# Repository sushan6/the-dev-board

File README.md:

# Sushan's dev board 

This development board is designed to be a compact, reliable prototyping platform using the RP2040 microcontroller. It handles power management, high-speed external memory routing, and precise clocking, making it ready for custom embedded software applications.

## Key Features

* Microcontroller: Based on the RP2040 chip, bringing twin-core processing capabilities to a custom hardware layout.
* Power Management: Driven by a modern USB-C receptacle for both power delivery and data interfacing, regulated down to a clean three-point-three volts using an onboard linear regulator.
* External Storage: Incorporates external flash memory connected over a quad serial peripheral interface, giving ample room for large programs and data storage.
* Clock Source: Utilises a twelve megahertz crystal oscillator circuit to ensure stable and highly accurate clock timing for the microcontroller.
* Input and Output Breakouts: Exposes general-purpose input/output pins to dual-row pin headers, providing quick access for connecting sensors, displays, and external components.
* There are 40 pins externally for data
* SD card reader 
## Hardware Design and Previews

### Schematic Layout
The schematic is divided into clean functional blocks including power management, flash memory wiring, crystal clock generation, and pin mappings. 

---

### PCB Layout and 3D Visualisations
The physical layout focuses on tight trace routing, proper decoupling capacitor placement for power stability, and optimised signal paths. 

#### Board Front View

#### Board Back View

## Bill of Materials (BOM)

### Main BOM

| **Item** | **Link** | **Quantity** | **Cost (USD)** |
|---|---|---:|---:|
| 1 µF Capacitors (0402) | [Robu.in](https://robu.in/product/1uf-capacitor-smdc-0402-pack-of-50/) | 20 | $0.06 |
| 100 nF Capacitors (0402) | [Robu.in](https://robu.in/product/0402b104j250nt-fh-25v-100nf-x7r%C2%B15-0402-multilayer-ceramic-capacitors-mlcc-smd-smt-rohs/) | 20 | $0.14 |
| 10 µF Capacitors (0603) | [Robu.in](https://robu.in/product/0603x106m100nt-fh-10v-10uf-x5r%C2%B120-0603-multilayer-ceramic-capacitors-mlcc-smd-smt-rohs/) | 20 | $0.53 |
| 33 pF Capacitors (0402) | [Robu.in](https://robu.in/product/0402cg330j160nt-fh-smd-multilayer-ceramic-capacitor-33-pf-16-v-0402-1005-metric-%25c2%25b1-5-c0g-np0/) | 20 | $0.01 |
| USB-C Receptacles | [LCSC India](https://lcscindia.com/part/TYPE-C-31-M-12) | 2 | $0.45 |
| 1×20 Pin Headers | [Robu.in](https://robu.in/product/ds1021-1x20sf11-b-connfly-1x20-pin-2-54mm-pin-header-v-t-type/) | 4 | $0.55 |
| MicroSD Card Connectors | [RS India](https://in.rsdelivers.com/product/molex/104031-0811/molex-104031-8-way-push-pull-microsd-memory-card/8967560) | 2 | $4.68 |
| 5.1 kΩ Resistors (0402) | [Robu.in](https://robu.in/product/rc0402fr-075k1l-yageo-res-thick-film-0402-5-1k-ohm-1-0-063w1-16w-%C2%B1100ppm-c-pad-smd-t-r/) | 20 | $0.05 |
| 27 Ω Resistors (0402) | [Robu.in](https://robu.in/product/rc0402jr-0727rl-yageo-res-thick-film-0402-27-ohm-5-0-063w1-16w-%25c2%25b1100ppm-c-pad-smd-t-r/) | 20 | $0.02 |
| 1 kΩ Resistors (0402) | [Robu.in](https://robu.in/product/rc0402fr-071kl-yageo-res-thick-film-0402-1k-ohm-1-0-063w1-16w-%C2%B1100ppm-c-pad-smd-t-r/) | 20 | $0.03 |
| 10 kΩ Resistors (0402) | [Robu.in](https://robu.in/product/10k-resistor-smdr-0402-pack-of-50/) | 20 | $0.07 |
| Tactile Switches | [Robu.in](https://robu.in/product/tsa010a2026b-bzcn-3mm-2mm-50ma-round-button-standing-paste-3-9mm-260gf-12v-smd-tactile-switches-rohs/) | 2 | $0.04 |
| RP2040 Microcontrollers | [Robocraze](https://robocraze.com/products/raspberry-pi-rp2040-microcontroller-ic-chip) | 2 | $1.36 |
| 3.3V Voltage Regulators | [Microchip](https://www.microchip.com/en-us/product/MCP1700) | 2 | $1.20 |
| 16 Mbit SPI Flash | [Lion Circuits](https://www.lioncircuits.com/parts/W25Q16JVUXIQ%20TR) | 2 | $4.88 |
| 12 MHz Crystals | [Robu.in](https://robu.in/product/ysx321sl-12mhz-12pf-10ppm-4pins-smd-smt-metal-surface-quartz-crystal-pack-of-2/) | 2 | $0.43 |
| Soldering Starter Kit | [Robu.in](https://robu.in/product/soldering-starter-tool-kit-30w-iron-solder-sponge/) | 1 | $13.30 |
| Custom PCB | [JLCPCB](https://jlcpcb.com/) | 2 | $15.00 |

### Cost Summary

| **Item** | **Cost (USD)** |
|---|---:|
| Capacitors (20 each) | $0.75 |
| Resistors (20 each) | $0.16 |
| USB-C Receptacles | $0.45 |
| 1×20 Pin Headers | $0.55 |
| MicroSD Connectors | $4.68 |
| Tactile Switches | $0.04 |
| RP2040 Microcontrollers | $1.36 |
| Voltage Regulators | $1.20 |
| SPI Flash Memory | $4.88 |
| 12 MHz Crystals | $0.43 |
| Soldering Starter Kit | $13.30 |
| PCB Fabrication | $15.00 |
| **Total** | **$42.80** |

Note: Some items are ordered in multipe quantity because of minimum order value

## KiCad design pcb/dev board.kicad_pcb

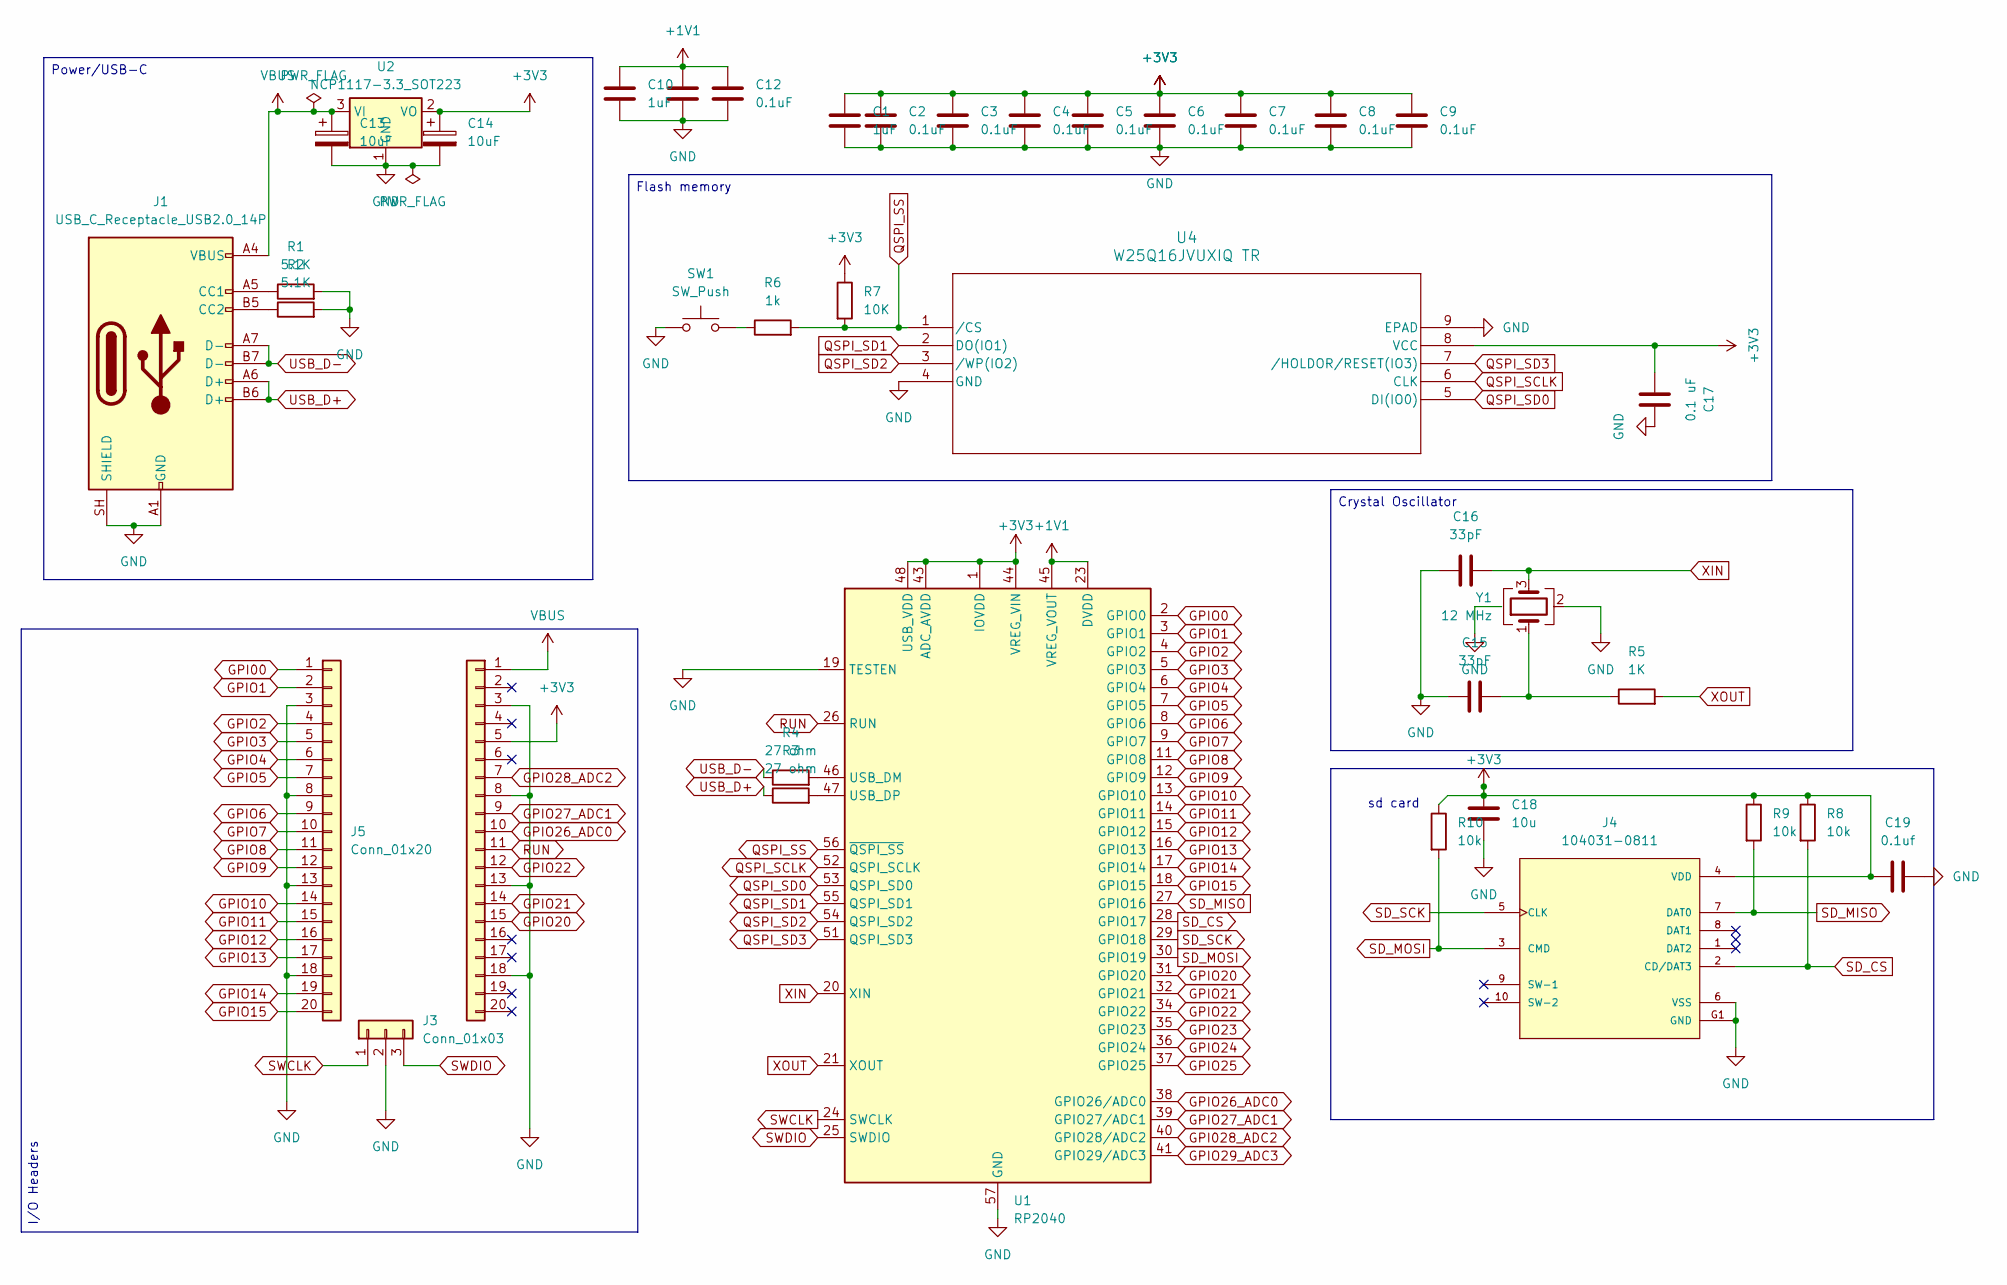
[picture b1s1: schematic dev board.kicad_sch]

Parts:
C1, C10: 1uF; C_0402_1005Metric
C2, C3, C4, C5, C6, C7, C8, C9, C11, C12: 0.1uF; C_0402_1005Metric
C13, C14: 10uF; C_0603_1608Metric
C15, C16: 33pF; C_0402_1005Metric
C17: 0.1 uF; C_0402_1005Metric
C18: 10u; C_0603_1608Metric
C19: 0.1uf; C_0402_1005Metric
J1: USB_C_Receptacle_USB2.0_14P; USB_C_Receptacle_HRO_TYPE-C-31-M-12
J2, J5: Conn_01x20; PinHeader_1x20_P2.54mm_Vertical
J3: Conn_01x03; PinHeader_1x03_P1.27mm_Vertical_SMD_Pin1Left
J4: 104031-0811; microSD_HC_Molex_104031-0811; PARTREV B2
R1, R2: 5.1K; R_0402_1005Metric
R3, R4: 27 ohm; R_0402_1005Metric
R5: 1K; R_0402_1005Metric
R6: 1k; R_0402_1005Metric
R7: 10K; R_0402_1005Metric
R8, R9, R10: 10k; R_0402_1005Metric
SW1: SW_Push; SW_Push_SPST_NO_Alps_SKRK
U1: RP2040; QFN-56-1EP_7x7mm_P0.4mm_EP3.2x3.2mm
U2: NCP1117-3.3_SOT223; SOT-23
U4: W25Q16JVUXIQ TR; Winbond_USON-8-1EP_3x2mm_P0.5mm_EP0.2x1.6mm
Y1: 12 MHz; Crystal_SMD_3225-4Pin_3.2x2.5mm

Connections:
+1V1: C10.1, C11.1, C12.1, U1.23 (DVDD), U1.45 (VREG_VOUT), U1.50 (DVDD)
+3V3: C1.1, C2.1, C3.1, C4.1, C5.1, C6.1, C7.1, C8.1, C9.1, C14.1, C17.1, C18.1, C19.2, J2.5, J4.4 (VDD), R7.1, R8.1, R9.1, R10.1, U1.1 (IOVDD), U1.10 (IOVDD), U1.22 (IOVDD), U1.33 (IOVDD), U1.42 (IOVDD), U1.43 (ADC_AVDD), U1.44 (VREG_VIN), U1.48 (USB_VDD), U1.49 (IOVDD), U2.2 (VO), U4.8 (VCC)
GND: C1.2, C2.2, C3.2, C4.2, C5.2, C6.2, C7.2, C8.2, C9.2, C10.2, C11.2, C12.2, C13.2, C14.2, C15.1, C16.1, C17.2, C18.2, C19.1, J1.A1 (GND), J1.A12 (GND), J1.B1 (GND), J1.B12 (GND), J1.SH (SHIELD), J2.3, J2.8, J2.13, J2.18, J3.2, J4.6 (VSS), J4.G1 (GND), J4.G2 (GND), J4.G3 (GND), J4.G4 (GND), J5.3, J5.8, J5.13, J5.18, R1.2, R2.2, SW1.1, U1.19 (TESTEN), U1.57 (GND), U2.1 (GND), U4.4 (GND), U4.9 (EPAD), Y1.2 (G), Y1.4 (G)
GPI00: J5.1
GPI028_ADC2: U1.40 (GPIO28/ADC2)
GPIO0: U1.2 (GPIO0)
GPIO1: J5.2, U1.3 (GPIO1)
GPIO2: J5.4, U1.4 (GPIO2)
GPIO3: J5.5, U1.5 (GPIO3)
GPIO4: J5.6, U1.6 (GPIO4)
GPIO5: J5.7, U1.7 (GPIO5)
GPIO6: J5.9, U1.8 (GPIO6)
GPIO7: J5.10, U1.9 (GPIO7)
GPIO8: J5.11, U1.11 (GPIO8)
GPIO9: J5.12, U1.12 (GPIO9)
GPIO10: J5.14, U1.13 (GPIO10)
GPIO11: J5.15, U1.14 (GPIO11)
GPIO12: J5.16, U1.15 (GPIO12)
GPIO13: J5.17, U1.16 (GPIO13)
GPIO14: J5.19, U1.17 (GPIO14)
GPIO15: J5.20, U1.18 (GPIO15)
GPIO20: J2.15, U1.31 (GPIO20)
GPIO21: J2.14, U1.32 (GPIO21)
GPIO22: J2.12, U1.34 (GPIO22)
GPIO23: U1.35 (GPIO23)
GPIO24: U1.36 (GPIO24)
GPIO25: U1.37 (GPIO25)
GPIO26_ADC0: J2.10, U1.38 (GPIO26/ADC0)
GPIO27_ADC1: J2.9, U1.39 (GPIO27/ADC1)
GPIO28_ADC2: J2.7
GPIO29_ADC3: U1.41 (GPIO29/ADC3)
unnamed: C15.2, R5.1, Y1.1
unnamed: J1.A5 (CC1), R1.1
unnamed: J1.B5 (CC2), R2.1
unnamed: R6.1, SW1.2
unnamed: R4.2, U1.46 (USB_DM)
unnamed: R3.2, U1.47 (USB_DP)
QSPI_SCLK: U1.52 (QSPI_SCLK), U4.6 (CLK)
QSPI_SD0: U1.53 (QSPI_SD0), U4.5 (DI(IO0))
QSPI_SD1: U1.55 (QSPI_SD1), U4.2 (DO(IO1))
QSPI_SD2: U1.54 (QSPI_SD2), U4.3 (/WP(IO2))
QSPI_SD3: U1.51 (QSPI_SD3), U4.7 (/HOLDOR/RESET(IO3))
QSPI_SS: R6.2, R7.2, U1.56 (~QSPI_SS), U4.1 (/CS)
RUN: J2.11, U1.26 (RUN)
SD_CS: J4.2 (CD/DAT3), R8.2, U1.28 (GPIO17)
SD_MISO: J4.7 (DAT0), R9.2, U1.27 (GPIO16)
SD_MOSI: J4.3 (CMD), R10.2, U1.30 (GPIO19)
SD_SCK: J4.5 (CLK), U1.29 (GPIO18)
SWCLK: J3.1, U1.24 (SWCLK)
SWDIO: J3.3, U1.25 (SWDIO)
USB_D+: J1.A6 (D+), J1.B6 (D+), R3.1
USB_D-: J1.A7 (D-), J1.B7 (D-), R4.1
VBUS: C13.1, J1.A4 (VBUS), J1.A9 (VBUS), J1.B4 (VBUS), J1.B9 (VBUS), J2.1, U2.3 (VI)
XIN: C16.2, U1.20 (XIN), Y1.3
XOUT: R5.2, U1.21 (XOUT)

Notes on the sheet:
sd card
Power/USB-C
I/O Headers
Flash memory
Crystal Oscillator

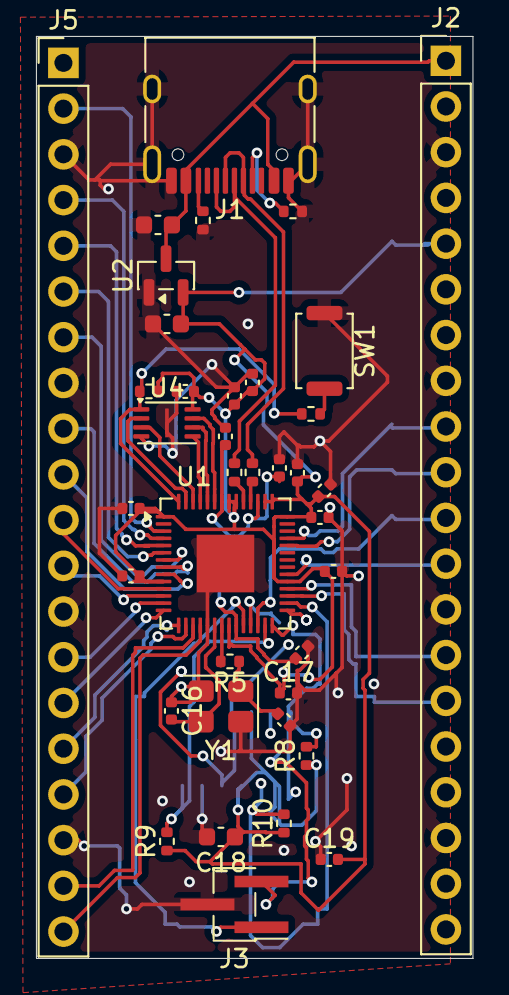
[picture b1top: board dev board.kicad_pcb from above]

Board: 4 copper layers, 24.2 x 51.2 mm, 39 parts (1 on the bottom side), 47 nets.

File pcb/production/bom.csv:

Designator,Footprint,Quantity,Value,LCSC Part #
"C1, C10",0402,2,1uF,
"C11, C12, C2, C3, C4, C5, C6, C7, C8, C9",0402,10,0.1uF,
"C13, C14",0603,2,10uF,
"C15, C16",0402,2,33pF,
C17,0402,1,0.1 uF,
J1,USB_C_Receptacle_HRO_TYPE-C-31-M-12,1,USB_C_Receptacle_USB2.0_14P,
"J2, J5",PinHeader_1x20_P2.54mm_Vertical,2,Conn_01x20,
J3,PinHeader_1x03_P2.54mm_Vertical,1,Conn_01x03,
"R1, R2",0402,2,5.1K,
"R3, R4",0402,2,27 ohm,
"R5, R6",0402,2,1K,
R7,0402,1,10K,
SW1,SW_Push_SPST_NO_Alps_SKRK,1,SW_Push,
U1,QFN-56-1EP_7x7mm_P0.4mm_EP3.2x3.2mm,1,RP2040,
U2,SOT-23,1,NCP1117-3.3_SOT223,
U4,Winbond_USON-8-1EP_3x2mm_P0.5mm_EP0.2x1.6mm,1,W25Q16JVUXIQ TR,
Y1,Crystal_SMD_3225-4Pin_3.2x2.5mm,1,12 MHz,

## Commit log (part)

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2026-05-13 Update README with project details and features
    Added project description and features to README.
2026-05-13 Fix formatting of Features section in README
    Corrected formatting of the Features section in README.
2026-06-29 Update fmt.Println message from 'Hello' to 'Goodbye'
2026-06-29 Remove empty schematic file
2026-06-29 Your custom commit message here
2026-06-29 Revise README for project overview and features
    Updated the README to provide a detailed project overview, key features, and hardware design information for the custom RP2040 development board.
2026-06-29 Add information about external data pins in README
